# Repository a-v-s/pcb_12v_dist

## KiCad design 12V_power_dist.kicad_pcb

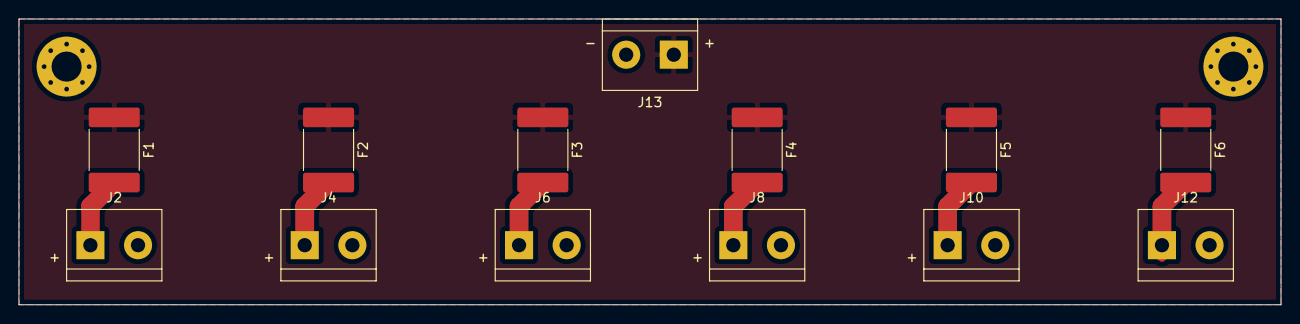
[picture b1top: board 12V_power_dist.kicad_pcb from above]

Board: 2 copper layers, 134.6 x 30.5 mm, 15 parts (0 on the bottom side), 8 nets.

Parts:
F1, F2, F3, F4, F5, F6: Polyfuse; Fuse_2920_7451Metric_Pad2.10x5.45mm_HandSolder
H1, H2: MountingHole; MountingHole_3.2mm_M3_Pad_Via
J2, J4, J6, J8, J10, J12, J13: Screw_Terminal_01x02; TerminalBlock_bornier-2_P5.08mm

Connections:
+12V: F1.1, F2.1, F3.1, F4.1, F5.1, F6.1, J13.1
GND: J2.2, J4.2, J6.2, J8.2, J10.2, J12.2, J13.2
unnamed: F1.2, J2.1
unnamed: F2.2, J4.1
unnamed: F3.2, J6.1
unnamed: F4.2, J8.1
unnamed: F5.2, J10.1
unnamed: F6.2, J12.1
